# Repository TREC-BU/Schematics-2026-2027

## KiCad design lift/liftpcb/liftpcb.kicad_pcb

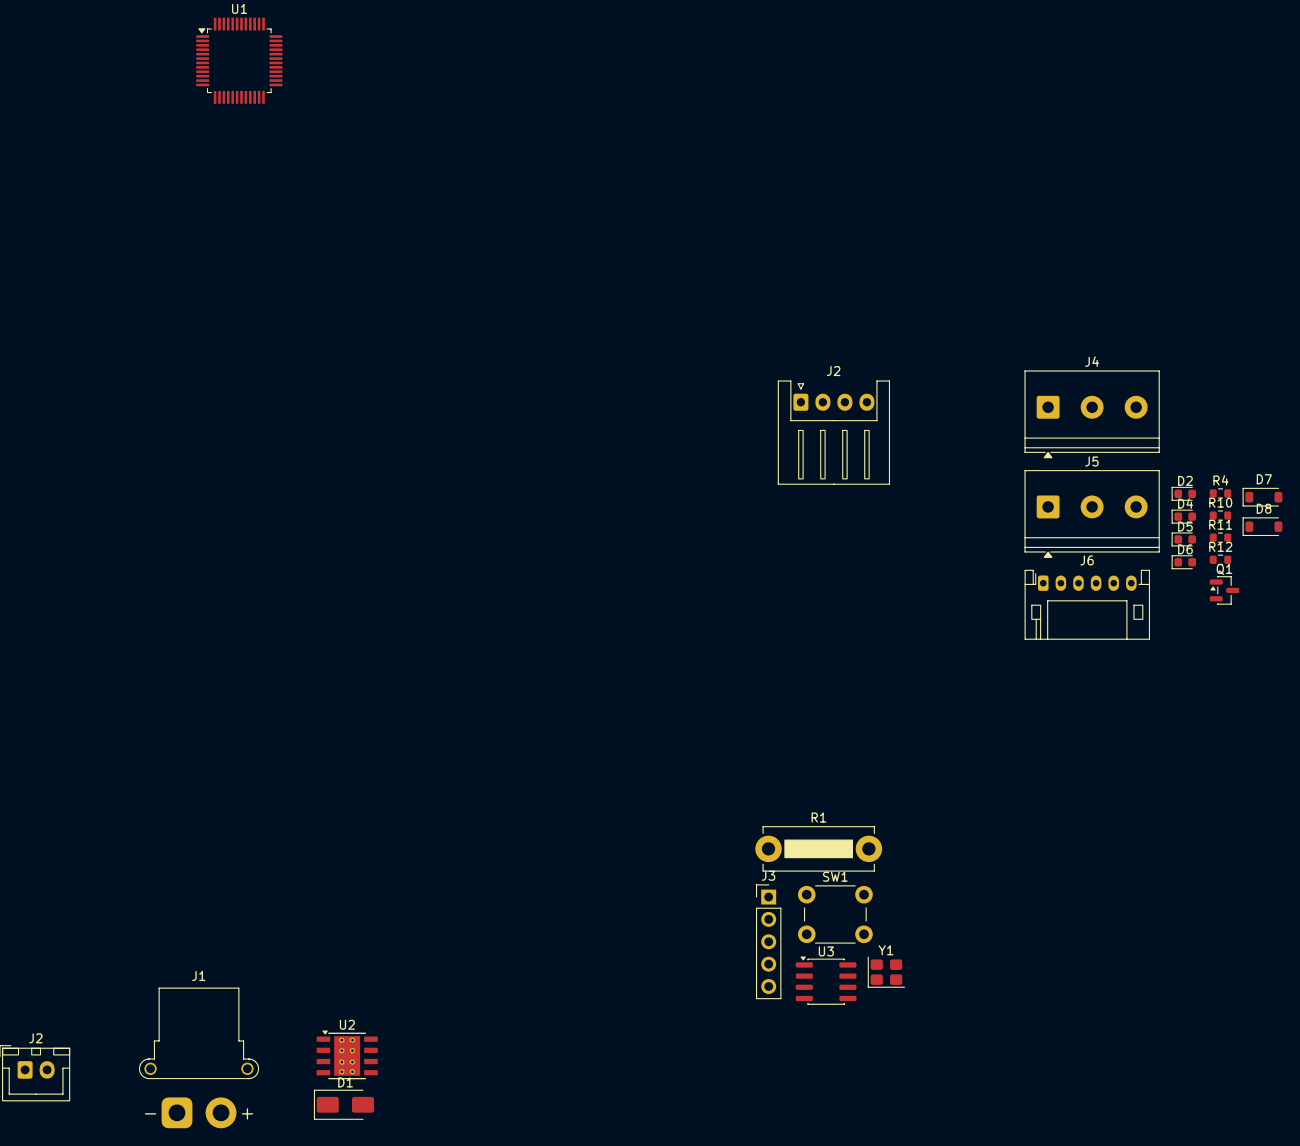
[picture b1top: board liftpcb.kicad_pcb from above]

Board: 2 copper layers, 25 parts (0 on the bottom side), 24 nets, no tracks yet.

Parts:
D1: SS34; D_SMA
D2: GRN; LED_0603_1608Metric
D4: YLW; LED_0603_1608Metric
D5: WHT; LED_0603_1608Metric
D6: RED; LED_0603_1608Metric
D7, D8: 1N4148W; D_SOD-123
J1: Conn_01x02_Socket; AMASS_XT30PW-F_1x02_P2.50mm_Horizontal
J2: Conn_01x02_Socket; JST_XH_B2B-XH-A_1x02_P2.50mm_Vertical
J2#2: Conn_01x04_Socket; JST_XH_S4B-XH-A_1x04_P2.50mm_Horizontal
J3: Conn_01x05_Pin; PinHeader_1x05_P2.54mm_Vertical
J4, J5: Screw_Terminal_01x03; TerminalBlock_Phoenix_PT-1,5-3-5.0-H_1x03_P5.00mm_Horizontal
J6: Conn_01x06_Socket; JST_PH_S6B-PH-K_1x06_P2.00mm_Horizontal
Q1: MMBT3904; SOT-23
R1: 120Ω; R_Bare_Metal_Element_L12.4mm_W4.8mm_P11.40mm
R4, R10: 10kΩ; R_0603_1608Metric
R11: 100Ω; R_0603_1608Metric
R12: 470Ω; R_0603_1608Metric
SW1: SW_Push; SW_PUSH_6mm_H5mm
U1: STM32C552CET6; LQFP-48_7x7mm_P0.5mm
U2: TPS5430DDA; TI_SO-PowerPAD-8_ThermalVias
U3: SN65HVD230DR; SOIC-8_3.9x4.9mm_P1.27mm
Y1: 24 MHz; Crystal_SMD_3225-4Pin_3.2x2.5mm

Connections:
+3.3V: J3.1, J6.1, U1.9 (VREF+), U1.24 (VDD), U1.36 (VDD), U1.48 (VDD), U3.3 (VCC)
+24V: D2.2 (A), D8.1 (K), J1.2, U2.7 (VIN)
CAN_H: J2#2.4, R1.1, U3.7 (CANH)
CAN_L: J2#2.3, R1.2, U3.6 (CANL)
CAN_RX: U1.32 (PA11), U3.4 (R)
CAN_TX: U1.33 (PA12), U3.1 (D)
COMM_LED: D5.2 (A), U1.18 (PB0)
FAULT_LED: D6.2 (A), U1.19 (PB1)
GND: D1.2 (A), D7.2 (A), J1.1, J3.5, J4.1, J5.2, J6.6, Q1.2 (E), R4.2, R10.2, R11.2, R12.2, SW1.1, U1.8 (VREF-), U1.23 (VSS), U1.35 (VSS), U1.47 (VSS), U2.6 (GND), U2.9 (GNDPAD), U3.2 (GND), U3.8 (Rs), Y1.2 (G), Y1.4 (G)
NRST: J3.3, SW1.2, U1.7 (NRST)
unnamed: D1.1 (K), U2.8 (PH)
unnamed: D2.1 (K), R4.1
unnamed: D4.1 (K), R10.1
unnamed: D5.1 (K), R11.1
unnamed: D6.1 (K), R12.1
OSC_IN: U1.5 (PH0-OSC_IN), Y1.1
OSC_OUT: U1.6 (PH1-OSC_OUT), Y1.3
PWR_COIL: D8.2 (A), Q1.3 (C)
S+24V: D4.2 (A), J5.3
SAFETY_COIL: D7.1 (K), J2#2.1
SWCLK: J3.2, U1.37 (PA14)
SWDIO: J3.4, U1.34 (PA13)
UART1_RX: J4.2, U1.31 (PA10)
UART1_TX: J4.3, U1.38 (PA15)
